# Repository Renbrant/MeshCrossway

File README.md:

# MeshCrossway for Android

**Two networks. Two radios. One app.** Use Meshtastic and MeshCore together on your Android phone, with messages, contacts and a shared map in one place.

Connect **two independent Bluetooth radios**: one running Meshtastic and one running MeshCore Companion BLE firmware. Each keeps its own network and conversations. MeshCrossway does not forward messages between the networks.

**[Download Android 0.4.8 beta](https://github.com/Renbrant/MeshCrossway/releases/download/android-v0.4.8/MeshCrossway-0.4.8.apk)** · [Visit the website](https://meshcrossway.renbrant.com/) · [Installation help](https://meshcrossway.renbrant.com/android/)

> Public beta for testing. Android 8.0+ on ARM64. Version 1.0 has not been released; compatibility and field testing continue.

Screenshots from beta 0.3.6; the current app may look different.

## What you can do

- Keep chats, channels, contacts and favorites from both networks together.
- Create and join channels, including sharing links and QR Codes.
- See nodes on one map, save places, record tracks and export GPX files.
- Download map areas before going offline.
- Follow your phone on the map, with an arrow showing your direction while moving.
- Customize colors, back up your data and use optional account and browser tools.
- Inspect and configure compatible MeshCore repeaters with administrator access.

Radio messages and saved offline maps work without cellular service. Internet is needed for app/map downloads and cloud features. Delivery depends on your radios, terrain and available mesh coverage.

## Get started

1. Download and open the APK on your Android phone. Allow installation when Android asks.
2. In Settings, connect your Meshtastic radio and your separate MeshCore radio. Close other apps connected to those radios first.
3. Wait for both networks to be ready, then open Chats or Map.

You choose and provide the radios. Heltec V3 radios are used in development; other models and firmware combinations need testing. A dedicated touchscreen controller is not required.

**Already using MeshCrossway?** Back up important data, then install the update over your existing app. **Do not uninstall or clear storage.** Versions 0.2.2 and earlier need the [one-time migration guide](docs/android-permanent-signing-backup.md).

## Latest improvements

**0.4.8 beta** adds GPS following and a movement arrow, building on simpler MeshCore repeater settings and protocol compatibility fixes. Map gestures pause following; tap GPS to resume. New behavior still needs field testing across supported setups. See the [release notes](https://github.com/Renbrant/MeshCrossway/releases/tag/android-v0.4.8).

## Guides and project information

- [Installation, compatibility and troubleshooting](docs/android-apk.md)
- [Channels, links and QR Codes](docs/android-channel-management.md)
- [Release history and version numbering](docs/android-version-history.md)
- [Android source and development guide](android/README.md)
- [ESP32 controller project and Web Flasher](https://meshcrossway.renbrant.com/esp32/) — secondary development track; stable firmware v0.10.5

## Contributing and license

Feedback, testing and contributions are welcome. [Report a problem](https://github.com/Renbrant/MeshCrossway/issues) with your app version, phone and radio models, or read [CONTRIBUTING.md](CONTRIBUTING.md).

Original project code and documentation use the [MIT License](LICENSE); see [licensing](docs/licensing.md) and [third-party notices](THIRD_PARTY_NOTICES.md). MeshCrossway is experimental and should not be your only means of communication in an emergency.

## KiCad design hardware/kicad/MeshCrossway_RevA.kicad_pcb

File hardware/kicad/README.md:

# MeshCrossway Rev A — KiCad project

This folder is the canonical home for the MeshCrossway Rev A KiCad design files and project-local footprint library.

## Current layout strategy

The Rev A schematic is shared by multiple PCB layout alternatives. The file `MeshCrossway_RevA.kicad_pcb` in this directory is the **active Layout B** and is intentionally blank/2-layer at the start so footprints can be pulled from the schematic with F8.

- **Layout A** — preserved alternative based on the earlier 4-layer engineering floorplan.
- **Layout B** — **active layout**, restarted from a blank PCB and targeting a **2-layer board**.
  - F.Cu: components, power and most signal routing.
  - B.Cu: keep as a nearly continuous GND reference plane; use bottom routing only when necessary and avoid cuts under RF modules or critical signals.

The schematic and footprints are common to both layouts. Do not duplicate or fork the schematic just to create a new PCB floorplan.

## Recommended project structure

```text
hardware/kicad/
├── MeshCrossway_RevA.kicad_pro
├── MeshCrossway_RevA.kicad_sch
├── MeshCrossway_RevA.kicad_pcb   # active Layout B
├── fp-lib-table
├── MeshCrossway.pretty/
│   ├── Waveshare_J8_Mating_2x16_P2.54mm.kicad_mod
│   ├── Module_XIAO_ESP32S3_WioSX1262_Socket.kicad_mod
│   ├── Module_LOCAL_5V_3Pin_Prototype.kicad_mod
│   └── Module_Uputronics_MAX_M10S_3V_MECH_APPROX.kicad_mod
└── layouts/
    ├── README.md
    ├── MeshCrossway_RevA_LAYOUT_A.kicad_pcb
    └── MeshCrossway_RevA_LAYOUT_B.kicad_pcb
```

The `layouts/*.kicad_pcb` files are alternatives. The schematic remains the electrical source of truth.

## Project-local footprint library

`fp-lib-table` registers:

```text
MeshCrossway -> ${KIPRJMOD}/MeshCrossway.pretty
```

When the project is opened from this folder, symbols that reference `MeshCrossway:<footprint>` resolve without any global KiCad-library configuration.

Current custom footprints:

- `Waveshare_J8_Mating_2x16_P2.54mm`
- `Module_XIAO_ESP32S3_WioSX1262_Socket`
- `Module_LOCAL_5V_3Pin_Prototype`
- `Module_Uputronics_MAX_M10S_3V_MECH_APPROX`

## Starting Layout B from scratch

1. Open `MeshCrossway_RevA.kicad_pro` from this directory.
2. Open the schematic and verify the project-local footprint library loads.
3. Create a blank PCB and save it as `layouts/MeshCrossway_RevA_LAYOUT_B.kicad_pcb`.
4. Open the existing blank `MeshCrossway_RevA.kicad_pcb` (already configured as a 2-layer starting board) or use `layouts/MeshCrossway_RevA_LAYOUT_B.kicad_pcb` as an untouched copy.
5. Use **Tools -> Update PCB from Schematic (F8)**.
6. Confirm zero footprint-library errors before applying the update.
7. Start with mechanical floorplanning only: J1, U2, U3 and U4. Do not route until the module positions and board outline are accepted.

## Fabrication gates

Before ordering a PCB, verify:

1. Waveshare J8 exact X/Y/orientation relative to the display PCB and mounting holes.
2. Waveshare mounting-hole drill diameter and exact mechanical coordinates.
3. Uputronics MAX-M10S header offset/orientation; the current module envelope is marked `MECH_APPROX`.
4. Exact `LOCAL_5V` regulator/module and final footprint.
5. XIAO/Wio stack height, USB-C access, U.FL pigtail bend radius, antenna keep-out and enclosure clearance.
6. Native KiCad ERC/DRC and zone refill.
7. For Layout B, preserve a nearly continuous B.Cu GND plane and review every bottom-layer trace for return-path disruption.

## Source control rules

Commit the actual design sources:

- `*.kicad_pro`
- `*.kicad_sch`
- `*.kicad_pcb`
- `*.kicad_mod`
- `fp-lib-table`

Do not commit editor locks, personal settings, autosaves or automatic backup folders. See `.gitignore` in this directory.

## Rev A battery mechanical envelope

For rear-side floorplanning, the project includes a mechanical-only footprint and a simple 3D envelope for the currently selected 1S LiPo battery:

- Footprint: `MeshCrossway:Battery_LiPo_10000mAh_110x60x12`
- 3D model: `${KIPRJMOD}/3dmodels/generated/Battery_LiPo_110x60x12.step`
- Nominal battery: 3.7 V, 10000 mAh, 37 Wh
- Envelope used: **110 x 60 x 12 mm**
- Advertised connector: **PH 2.0 mm**
- Advertised wire length: approximately **100 mm**
- Intended placement: **back side of the carrier PCB**

This is a **mechanical planning model**, based on the supplied product dimensions, not an official manufacturer CAD file. Verify the production battery dimensions, cable exit, connector polarity, swelling allowance, adhesive/foam thickness, and enclosure clearances before fabrication.

## Uputronics MAX-M10S mechanical model

The project includes an approximate 3D/mechanical model for the Uputronics u-blox MAX-M10S 3V breakout used in Rev A:

- Footprint: `MeshCrossway:Module_Uputronics_MAX_M10S_3V_MECH_APPROX`
- 3D model: `${KIPRJMOD}/3dmodels/generated/Uputronics_MAX-M10S_3V_MECH_APPROX.wrl`
- Published breakout PCB size: approximately **22 x 22 x 1.6 mm**
- Published header pitch: **2.54 mm**
- Published antenna connector: **SMA female**
- The model includes a simplified MAX-M10S, supercapacitor and edge-launch SMA.

The SMA barrel intentionally extends beyond the 22 mm PCB edge so the carrier PCB can be floorplanned with the GNSS antenna connector exposed at the enclosure/carrier edge. The exact SMA overhang and component placement are **mechanical approximations** because Uputronics does not publish a dimensioned CAD drawing for the complete assembled breakout. Verify against the physical module before fabrication.

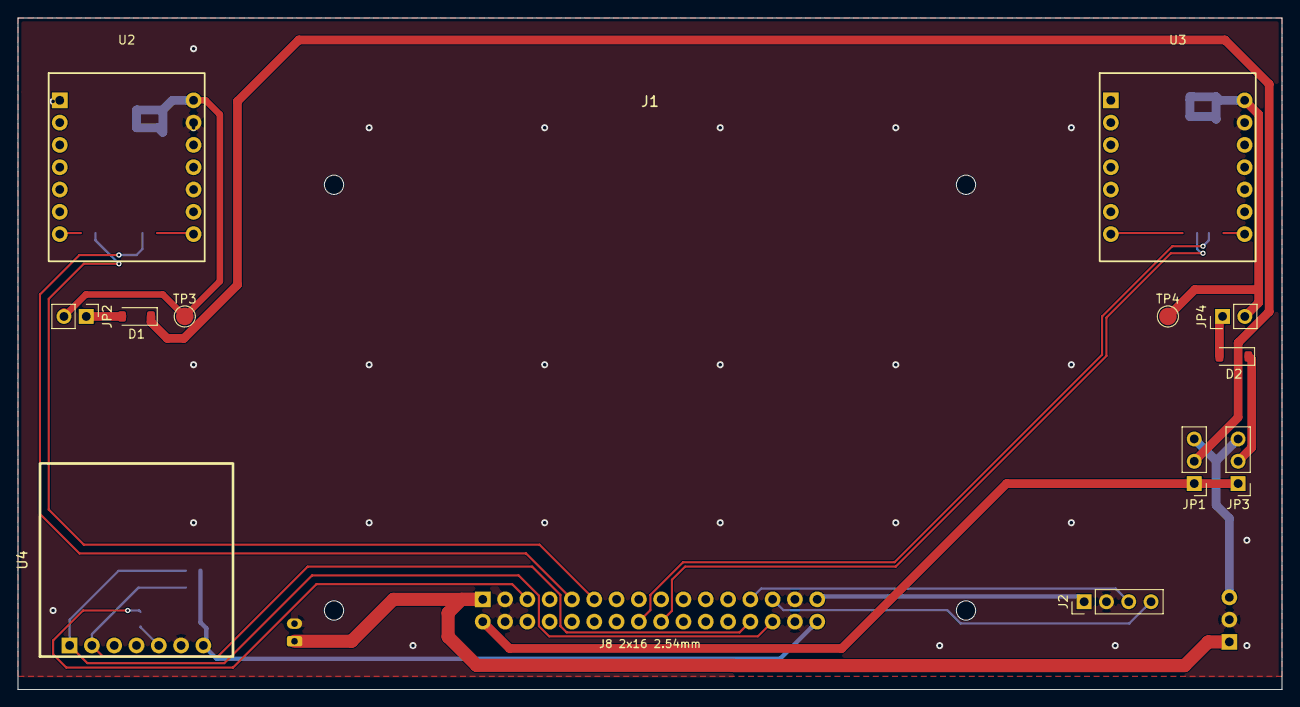
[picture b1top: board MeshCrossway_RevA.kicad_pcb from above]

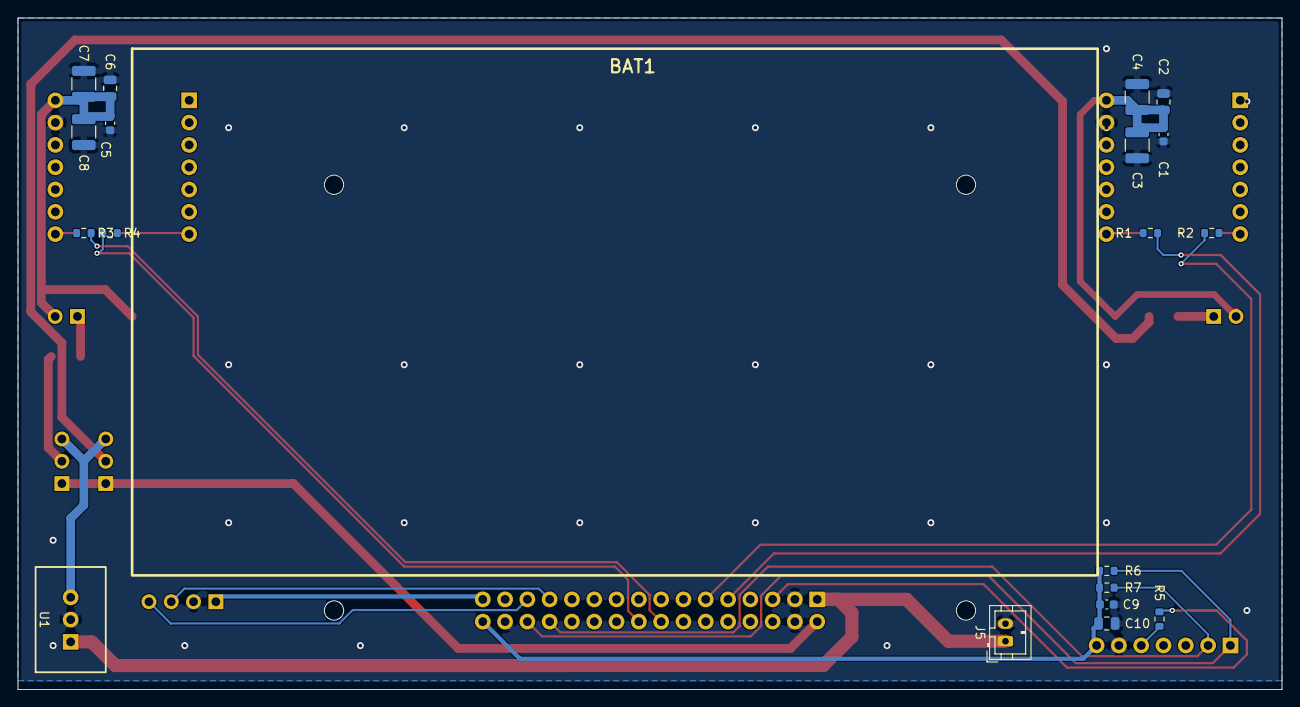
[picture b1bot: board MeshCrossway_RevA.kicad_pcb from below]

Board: 2 copper layers, 144.0 x 76.5 mm, 33 parts (20 on the bottom side), 25 nets.

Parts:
BAT1: LiPo 3.7V 10000mAh 110x60x12; Battery_LiPo_10000mAh_110x60x12
C1, C5, C9: 100nF; C_0603_1608Metric
C2, C6, C10: 10uF; C_0805_2012Metric
C3, C7: 47uF DNP; C_1210_3225Metric
C4, C8: 100uF DNP; C_1210_3225Metric
D1, D2: Schottky; D_SOD-123
J1: Waveshare ESP32-S3-Touch-LCD-3.5 — J8; Waveshare_J8_Mating_2x16_P2.54mm
J2: HOST DEBUG; PinHeader_1x04_P2.54mm_Vertical
J5: BATTERY JST-PH 2.0; JST_PH_B2B-PH-K_1x02_P2.00mm_Vertical
JP1: A POWER SELECT; PinHeader_1x03_P2.54mm_Vertical
JP2: A CURRENT LINK; PinHeader_1x02_P2.54mm_Vertical
JP3: B POWER SELECT; PinHeader_1x03_P2.54mm_Vertical
JP4: B CURRENT LINK; PinHeader_1x02_P2.54mm_Vertical
R1, R2, R3, R4: 47R; R_0603_1608Metric
R5: 0R; R_0603_1608Metric
R6, R7: 4.7k DNP; R_0603_1608Metric
TP3: RADIO_A_5V; TestPoint_Pad_D2.0mm
TP4: RADIO_B_5V; TestPoint_Pad_D2.0mm
U1: LOCAL 5V SOURCE — TBD; Module_LOCAL_5V_3Pin_Prototype
U2, U3: XIAO + Wio-SX1262; Module_XIAO_ESP32S3_WioSX1262_Socket
U4: Uputronics MAX-M10S 3V; Module_Uputronics_MAX_M10S_3V_MECH_APPROX

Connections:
/BAT: J1.1 (BAT), J5.1 (BAT+), U1.1 (VIN_BAT)
/GND: C1.2, C2.2, C3.2, C4.2, C5.2, C6.2, C7.2, C8.2, C9.2, C10.2, J1.3 (GND), J1.4 (GND), J1.29 (GND), J1.30 (GND), J2.2 (GND), J5.2 (GND), U1.2 (GND), U2.13 (GND), U3.13 (GND), U4.6 (GND)
/GNSS_PPS: J1.5 (GPIO21), R5.2
/GNSS_PPS_RAW: R5.1, U4.5 (TP/PPS)
/GNSS_SCL: J1.26 (SCL/GPIO7), R7.2, U4.2 (SCL)
/GNSS_SDA: J1.28 (SDA/GPIO8), R6.2, U4.1 (SDA)
/HOST_RXD: J1.25 (RXD/GPIO43), J2.3 (HOST_RXD)
/HOST_TXD: J1.27 (TXD/GPIO44), J2.4 (HOST_TXD)
/J8_3V3: C9.1, C10.1, J1.31 (3V3), J1.32 (3V3), J2.1 (3V3), R6.1, R7.1, U4.7 (VCC_3V3)
/J8_5V: J1.2 (5V), JP1.1 (SRC_A), JP3.1 (SRC_A)
/LOCAL_5V: JP1.3 (SRC_B), JP3.3 (SRC_B), U1.3 (VOUT_5V)
/MC_HOST_RX: J1.18 (GPIO18), R4.2
/MC_HOST_TX: J1.16 (GPIO17), R3.1
/MC_RADIO_RX: R3.2, U3.8 (D7/RX)
/MC_RADIO_TX: R4.1, U3.7 (D6/TX)
/MT_HOST_RX: J1.11 (GPIO40), R2.2
/MT_HOST_TX: J1.9 (GPIO39), R1.1
/MT_RADIO_RX: R1.2, U2.8 (D7/RX)
/MT_RADIO_TX: R2.1, U2.7 (D6/TX)
/RADIO_A_5V: C1.1, C2.1, C3.1, C4.1, JP2.2 (OUT), TP3.1 (TP_1), U2.14 (VBUS/5V)
/RADIO_B_5V: C5.1, C6.1, C7.1, C8.1, JP4.2 (OUT), TP4.1 (TP_1), U3.14 (VBUS/5V)
unnamed: D1.1 (A), JP1.2 (COMMON)
unnamed: D1.2 (K), JP2.1 (IN)
unnamed: D2.1 (A), JP3.2 (COMMON)
unnamed: D2.2 (K), JP4.1 (IN)

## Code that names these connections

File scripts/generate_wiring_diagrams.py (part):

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s.display(453,217,366,230)
s.card(980,194,255,265,'Radio B: MeshCore','XIAO ESP32S3 + Wio-SX1262',C['amber']);s.xiao(1018,275,.95,'MC');s.chip(1039,422,142,'LoRa • independent',C['amber'])
s.line(300,334,446,334,C['cyan'],3,True);s.chip(327,294,95,'UART1',C['cyan']);s.line(832,334,974,334,C['amber'],3,True);s.chip(861,294,95,'UART2',C['amber'])
s.card(55,528,250,103,'u-blox MAX-M10S','GNSS breakout + active antenna',C['teal']);s.lines(74,599,['I2C GPIO8/7 • PPS GPIO21'],24,14)
s.card(428,528,406,103,'ONE custom carrier PCB','Display + both radios + GNSS + service connectors',C['teal']);s.lines(450,598,['Battery mounted on the rear of the carrier'],23,14)
s.card(969,528,265,103,'Rear 1S LiPo battery','Protected cell + Waveshare AXP2101',C['amber']);s.lines(987,598,['Capacity / power path: unverified'],23,13)
s.path('M 287 528 V 491 H 520 V 468',C['teal'],2,True)
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# 3. Radio UART wiring
s=Art('Radio UART wiring','Both radios are 3.3 V serial peers; host TX must cross to radio RX','Candidate GPIO assignments require firmware-target and physical pinout verification on delivered boards.')
for x,title,sub,edge,rows in [
 (48,'A  Meshtastic','Serial Module: PROTO',C['cyan'],['Host GPIO39 TX  →  XIAO D7 / GPIO44 RX','Host GPIO40 RX  ←  XIAO D6 / GPIO43 TX','GND                 ↔  GND']),
 (667,'B  MeshCore','Serial Companion binary protocol',C['amber'],['Host GPIO17 TX  →  XIAO D7 / GPIO44 RX','Host GPIO18 RX  ←  XIAO D6 / GPIO43 TX','GND                 ↔  GND'])]:
 s.card(x,181,565,414,title,sub,edge,22)
 s.card(x+22,258,204,206,'Waveshare host','ESP32-S3 3.5-inch',edge,17)
 s.card(x+337,258,204,206,'XIAO / Wio','SX1262 radio module',edge,17)
 for i,row in enumerate(rows):
  yy=321+53*i
  src,dst=(('GPIO39','D7 / GPIO44'),('GPIO40','D6 / GPIO43'),('GND','GND'))[i] if x==48 else (('GPIO17','D7 / GPIO44'),('GPIO18','D6 / GPIO43'),('GND','GND'))[i]
  s.chip(x+37,yy,166,src,edge);s.chip(x+354,yy,166,dst,edge)
  s.line(x+226,yy+12,x+332,yy+12,edge,2.5,i!=1)
  if i==1:s.path(f'M {x+332} {yy+18} H {x+226}',edge,2.5,True)
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# 4. Connector reference
s=Art('Connector reference','Physical signal identity only: do not infer J8 position numbering from marketing photos','Use actual PCB revision/schematic. Meshtastic D6/D7 and MeshCore D6/D7 need confirmed free GPIOs.')
s.card(50,185,530,415,'Waveshare host expansion (J8)','Board revision and pin numbering must be inspected',C['cyan'])
s.lines(77,277,['GPIO39   →  UART1 TX → Meshtastic RX','GPIO40   ←  UART1 RX ← Meshtastic TX','GPIO17   →  UART2 TX → MeshCore RX','GPIO18   ←  UART2 RX ← MeshCore TX','GPIO8 ↔ GNSS SDA • GPIO7 ↔ SCL','GPIO21 ← GNSS PPS/TP via 0R','Radio power: J8 5V / LOCAL_5V → VBUS'],42,17)
s.card(625,185,604,183,'Radio A  •  Meshtastic','XIAO D7 / GPIO44 RX      XIAO D6 / GPIO43 TX',C['cyan']);s.xiao(669,256,.75,'MT');s.lines(867,280,['Serial PROTO','115200 baud (verify)','Shared GND'],28,15)
s.card(625,402,604,198,'Radio B  •  MeshCore','XIAO D7 / GPIO44 RX     XIAO D6 / GPIO43 TX',C['amber']);s.xiao(670,480,.75,'MC');s.lines(868,503,['Companion Serial','115200 baud (verify)','Shared GND'],27,15)
s.save('connector-reference.svg')

# 5. Full wiring
s=Art('Wiring diagram','UART, GNSS I2C/PPS and grounds — Rev A carrier pin contract, NOT a fabrication schematic','Radio power uses selectable J8/local 5 V into XIAO VBUS; current/backfeed remain bench gates.')
s.card(45,175,337,437,'Waveshare ESP32-S3 host','No camera; two UARTs + GNSS I2C',C['cyan'])
s.lines(63,260,['GPIO39  •  UART1 TX','GPIO40  •  UART1 RX','GPIO17  •  UART2 TX','GPIO18  •  UART2 RX','GPIO8   •  GNSS SDA','GPIO7   •  GNSS SCL','GPIO21  •  GNSS PPS','GND • common • GNSS on J8 3V3','5V • J8/local selectable for radios'],42,17)
s.card(537,175,698,140,'Radio A  /  Meshtastic','Seeed XIAO ESP32S3 + Wio-SX1262',C['cyan'])
s.lines(563,243,['RX  D7/GPIO44 ← Host GPIO39 TX','TX  D6/GPIO43 → Host GPIO40 RX','GND ↔ Host GND  •  PROTO 115200'],22,16)
s.card(537,331,698,140,'Radio B  /  MeshCore','Seeed XIAO ESP32S3 + Wio-SX1262',C['amber'])
s.lines(563,400,['RX  D7/GPIO44 ← Host GPIO17 TX','TX  D6/GPIO43 → Host GPIO18 RX','GND ↔ Host GND  •  Companion 115200'],22,16)
s.card(537,487,698,125,'G1  /  u-blox MAX-M10S','Selected 3 V breakout with active GNSS antenna (bias to verify)',C['teal'])
s.lines(563,557,['SDA ↔ GPIO8  |  SCL ↔ GPIO7  |  PPS → GPIO21  |  GND'],24,15)
for y,cl in [(259,C['cyan']),(416,C['amber']),(554,C['teal'])]:s.path(f'M 382 {y} H 500 V {y-15} H 530',cl,2.5,True)
s.save('architecture/wiring-diagram.svg')

# 6. GNSS and power
s=Art('GNSS + battery layout','MAX-M10S I2C remains central; battery moves behind the carrier and screen','Confirm GNSS antenna bias, LiPo protection/connector polarity, battery fit, and power-source isolation.')
s.card(58,187,342,420,'Waveshare / AXP2101','Host charger and power management',C['cyan'])
s.lines(81,291,['USB-C 5 V → internal power path','Protected 1S LiPo → BAT port','Host GNSS SDA: GPIO8 / J8-28','Host GNSS SCL: GPIO7 / J8-26','GNSS PPS: GPIO21 / J8-5','Ground: common reference'],43,17)
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s.card(845,187,379,420,'Rear mounted LiPo','Physically behind the screen/carrier',C['amber']);s.battery(923,295,215,124);s.lines(868,469,['3.7 V nominal protected cell','Do not parallel XIAO charger systems','Battery thickness and safety checks','Radio VBUS: J8 5V / LOCAL_5V selectable'],29,15)
s.line(400,360,448,360,C['teal'],3,True);s.path('M 784 420 H 824 V 448 H 844',C['amber'],2,True)
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# 7. Power architecture
s=Art('Power architecture','Rev A radios use independently selectable 5 V sources into XIAO VBUS','VALIDATE: J8 5 V headroom, LOCAL_5V, Schottky drop, USB backfeed and TX transients.')
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s.card(860,173,366,135,'Radio A + Radio B','2 × XIAO VBUS via independent selectors',C['amber']);s.card(860,354,366,127,'u-blox MAX-M10S','J8 3V3 • I2C GPIO8/7 • PPS GPIO21',C['teal']);s.chip(929,533,217,'5V PATH • VALIDATE',C['warn'])
s.line(269,249,351,249,C['cyan'],2.5,True);s.path('M 270 433 H 324 V 441 H 353',C['amber'],2.5,True);s.path('M 718 325 H 802 V 240 H 855',C['amber'],2.5,True);s.path('M 718 399 H 802 V 422 H 855',C['teal'],2.5,True)
s.save('architecture/power-architecture.svg')

# 8. Communication stack
s=Art('Communication stack','One shared UI; two independent native mesh protocols','Never silently bridge Meshtastic to MeshCore, share keys or imply inter-protocol routing.')
s.card(314,130,652,92,'Touchscreen application','Waveshare LVGL: chat / map / contacts / settings',C['cyan']);s.card(314,250,652,96,'Core host services','Message history • GNSS • protocol adapters • queues',C['purple']);s.line(640,222,640,245,C['cyan'],3,True)
s.card(54,388,547,240,'Meshtastic path  /  UART1','PROTO binary frames, ToRadio / FromRadio',C['cyan']);s.lines(78,466,['XIAO ESP32S3 + Wio-SX1262','Native Meshtastic routing and channel model','LoRa RF → Meshtastic network','Host GPIO39/40 ↔ XIAO GPIO44/43'],36,17)
s.card(677,388,547,240,'MeshCore path  /  UART2','Companion binary command / response / events',C['amber']);s.lines(705,466,['XIAO ESP32S3 + Wio-SX1262','Native MeshCore contacts and path model','LoRa RF → MeshCore network','Host GPIO17/18 ↔ XIAO GPIO44/43'],36,17)
s.path('M 539 346 V 369 H 329 V 383',C['cyan'],2.5,True);s.path('M 744 346 V 369 H 950 V 383',C['amber'],2.5,True)
s.save('architecture/communication-stack.svg')

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s.save('architecture/direct-tracking-modes.svg')

# 11. XIAO board-to-board radio wiring (host UART versus internal SX1262 SPI)
s=Art('XIAO/Wio internal vs external links','Never wire Waveshare to SX1262 SPI or DIO; the Seeed B2B module is managed by each XIAO MCU','Rev A external UART: D6/TX GPIO43 and D7/RX GPIO44; firmware/bench validation still required.')
s.card(40,188,288,385,'Waveshare touch host','ESP32-S3 3.5-inch display',C['cyan'])
s.lines(65,281,['UART1 TX GPIO39','UART1 RX GPIO40','UART2 TX GPIO17','UART2 RX GPIO18','Common GND'],45,17)
for y,name,col,num in [(175,'A / Meshtastic',C['cyan'],1),(386,'B / MeshCore',C['amber'],2)]:
 s.card(402,y,322,183,'XIAO ESP32S3 • '+name,'Seeed B2B kit • external UART',col,16)
 s.lines(422,y+77,['D7/GPIO44 = radio UART RX','D6/GPIO43 = radio UART TX','MCU manages SX1262 over B2B'],28,14)
 s.card(813,y,412,183,'Wio-SX1262 (internal)','Radio daughterboard, NOT host UART',col,19)
 s.lines(834,y+78,['SX1262 connected to XIAO via B2B','SPI + DIO/RESET/BUSY per variant','LoRa U.FL → separate 900 MHz antenna'],27,15)
 s.path(f'M 329 {y+88} H 390',col,2.5,True)
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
